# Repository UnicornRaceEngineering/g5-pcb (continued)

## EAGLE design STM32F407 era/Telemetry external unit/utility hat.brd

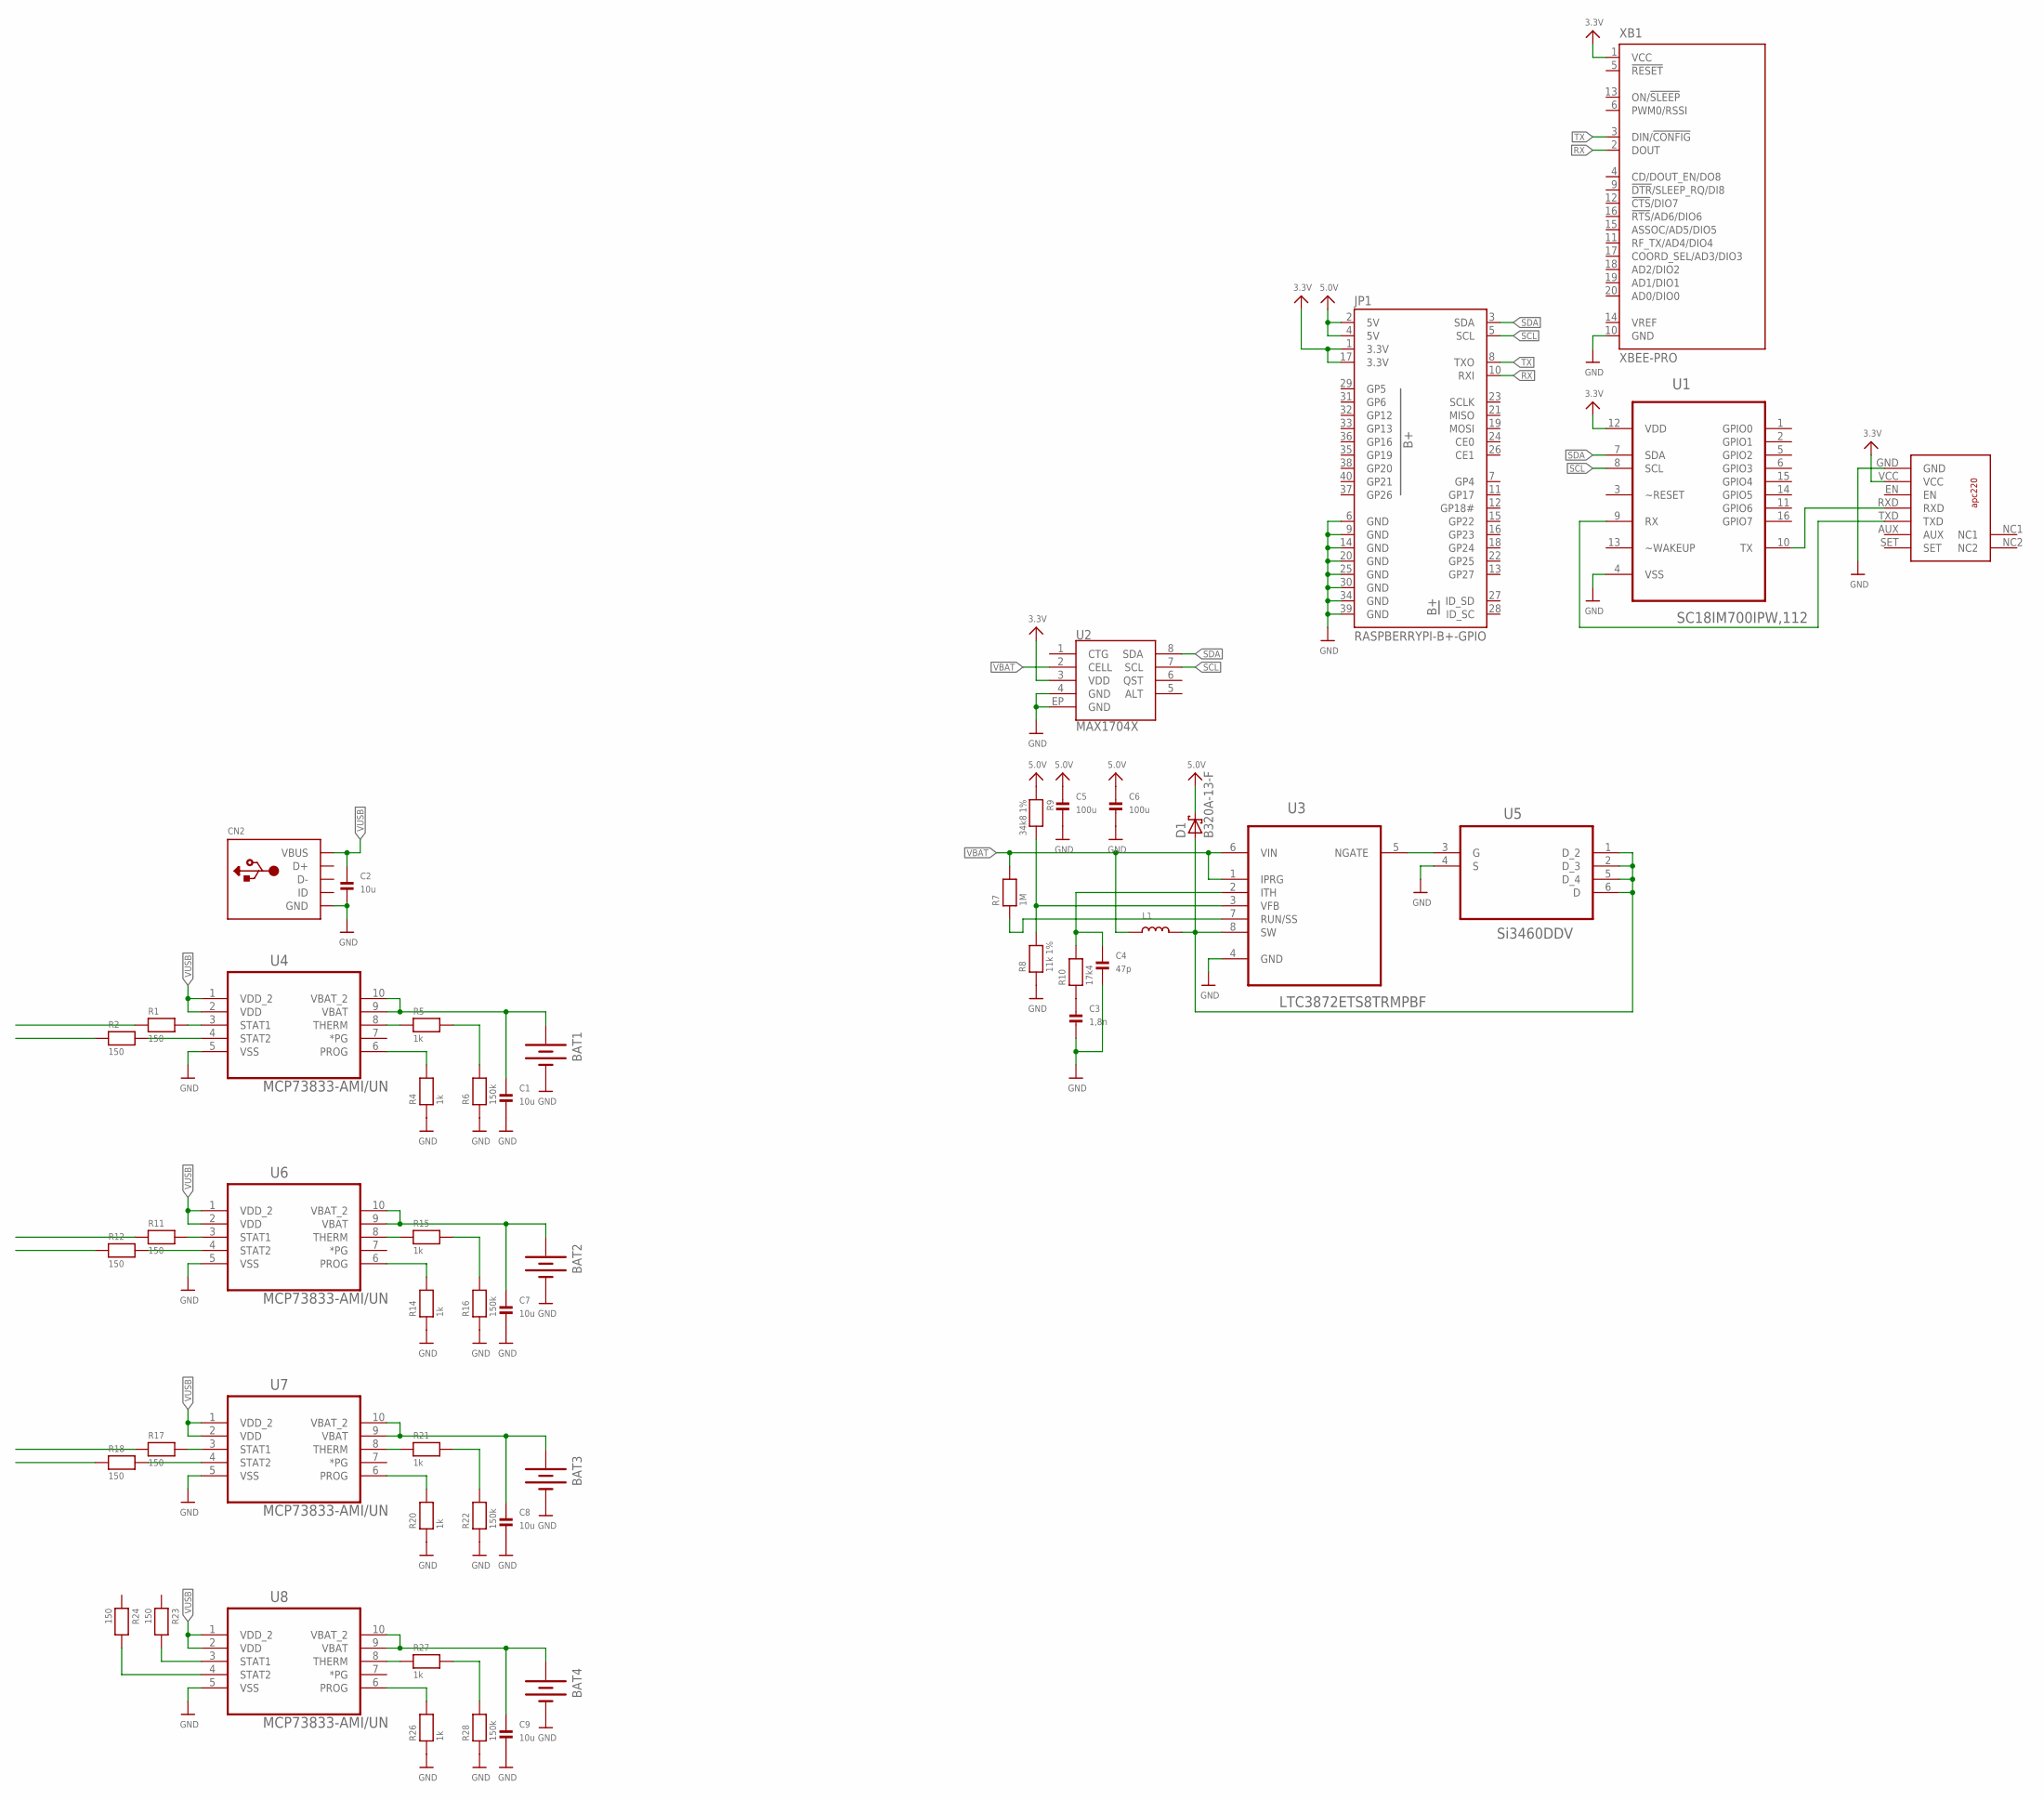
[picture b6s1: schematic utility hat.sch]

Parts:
BAT1, BAT2, BAT3, BAT4: BATTERY18650; BATTERY_18650-HOLDER
C1, C2, C7, C8, C9: 10u; _0805MP
C3: 1,8n; _0603MP
C4: 47p; _0603MP
C5, C6: 100u; 1206
CN2: USBMINIB; USB-MINIB
D1: B320A-13-F; SMC
JP1: RASPBERRYPI-B+-GPIO; 2X20-SHROUDED
L1: INDUCTOR; INDUCTOR_1007
R1, R2, R11, R12, R17, R18, R23, R24: 150; _0603MP
R4, R5, R14, R15, R20, R21, R26, R27: 1k; _0603MP
R6, R16, R22, R28: 150k; _0603MP
R7: 1M; _0603MP
R8: 11k 1%; _0603MP
R9: 34k8 1%; _0603MP
R10: 17k4; _0603MP
U1: SC18IM700IPW,112; SOP65P640X110-16N
U2: MAX1704X; TDFN-8
U3: LTC3872ETS8TRMPBF; SOT65P280X100-8N
U4, U6, U7, U8: MCP73833-AMI/UN; SOP50P490X110-10N
U5: Si3460DDV; SOT95P285X110-6N
U$10: APC220
XB1: XBEE-PRO

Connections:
3.3V: JP1.1 (3.3V), JP1.17 (3.3V), U1.12 (VDD), U2.3 (VDD), U$10.VCC, XB1.1 (VCC)
5.0V: C5.1, C6.1, D1.C, JP1.2 (5V), JP1.4 (5V), R9.1
GND: BAT1.GND@1 (-), BAT2.GND@1 (-), BAT3.GND@1 (-), BAT4.GND@1 (-), C1.2, C2.2, C3.2, C4.2, C5.2, C6.2, C7.2, C8.2, C9.2, CN2.GND, JP1.6 (GND), JP1.9 (GND), JP1.14 (GND), JP1.20 (GND), JP1.25 (GND), JP1.30 (GND), JP1.34 (GND), JP1.39 (GND), R4.1, R6.1, R8.1, R14.1, R16.1, R20.1, R22.1, R26.1, R28.1, U1.4 (VSS), U2.4 (GND), U2.EP (GND), U3.4 (GND), U4.5 (VSS), U5.4 (S), U6.5 (VSS), U7.5 (VSS), U8.5 (VSS), U$10.GND, XB1.10 (GND)
unnamed: U1.10 (TX), U$10.RXD
unnamed: U1.9 (RX), U$10.TXD
unnamed: R1.2, U4.3 (STAT1)
unnamed: R2.2, U4.4 (STAT2)
unnamed: R4.2, U4.6 (PROG)
unnamed: R5.1, U4.8 (THERM)
unnamed: R5.2, R6.2
unnamed: R7.1, U3.7 (RUN/SS)
unnamed: R8.2, R9.2, U3.3 (VFB)
unnamed: C4.1, R10.2, U3.2 (ITH)
unnamed: C3.1, R10.1
unnamed: D1.A, L1.P$2 (2), U3.8 (SW), U5.1 (D_2), U5.2 (D_3), U5.5 (D_4), U5.6 (D)
unnamed: U3.5 (NGATE), U5.3 (G)
unnamed: BAT1.PWR@1 (+), C1.1, U4.9 (VBAT), U4.10 (VBAT_2)
unnamed: R11.2, U6.3 (STAT1)
unnamed: R12.2, U6.4 (STAT2)
unnamed: R14.2, U6.6 (PROG)
unnamed: R15.1, U6.8 (THERM)
unnamed: R15.2, R16.2
unnamed: BAT2.PWR@1 (+), C7.1, U6.9 (VBAT), U6.10 (VBAT_2)
unnamed: R17.2, U7.3 (STAT1)
unnamed: R18.2, U7.4 (STAT2)
unnamed: R20.2, U7.6 (PROG)
unnamed: R21.1, U7.8 (THERM)
unnamed: R21.2, R22.2
unnamed: BAT3.PWR@1 (+), C8.1, U7.9 (VBAT), U7.10 (VBAT_2)
unnamed: R23.2, U8.3 (STAT1)
unnamed: R24.2, U8.4 (STAT2)
unnamed: R26.2, U8.6 (PROG)
unnamed: R27.1, U8.8 (THERM)
unnamed: R27.2, R28.2
unnamed: BAT4.PWR@1 (+), C9.1, U8.9 (VBAT), U8.10 (VBAT_2)
RX: JP1.10 (RXI), XB1.2 (DOUT)
SCL: JP1.5 (SCL), U1.8 (SCL), U2.7 (SCL)
SDA: JP1.3 (SDA), U1.7 (SDA), U2.8 (SDA)
TX: JP1.8 (TXO), XB1.3 (DIN/!CONFIG)
VBAT: L1.P$1 (1), R7.2, U2.2 (CELL), U3.1 (IPRG), U3.6 (VIN)
VUSB: C2.1, CN2.VBUS, U4.1 (VDD_2), U4.2 (VDD), U6.1 (VDD_2), U6.2 (VDD), U7.1 (VDD_2), U7.2 (VDD), U8.1 (VDD_2), U8.2 (VDD)

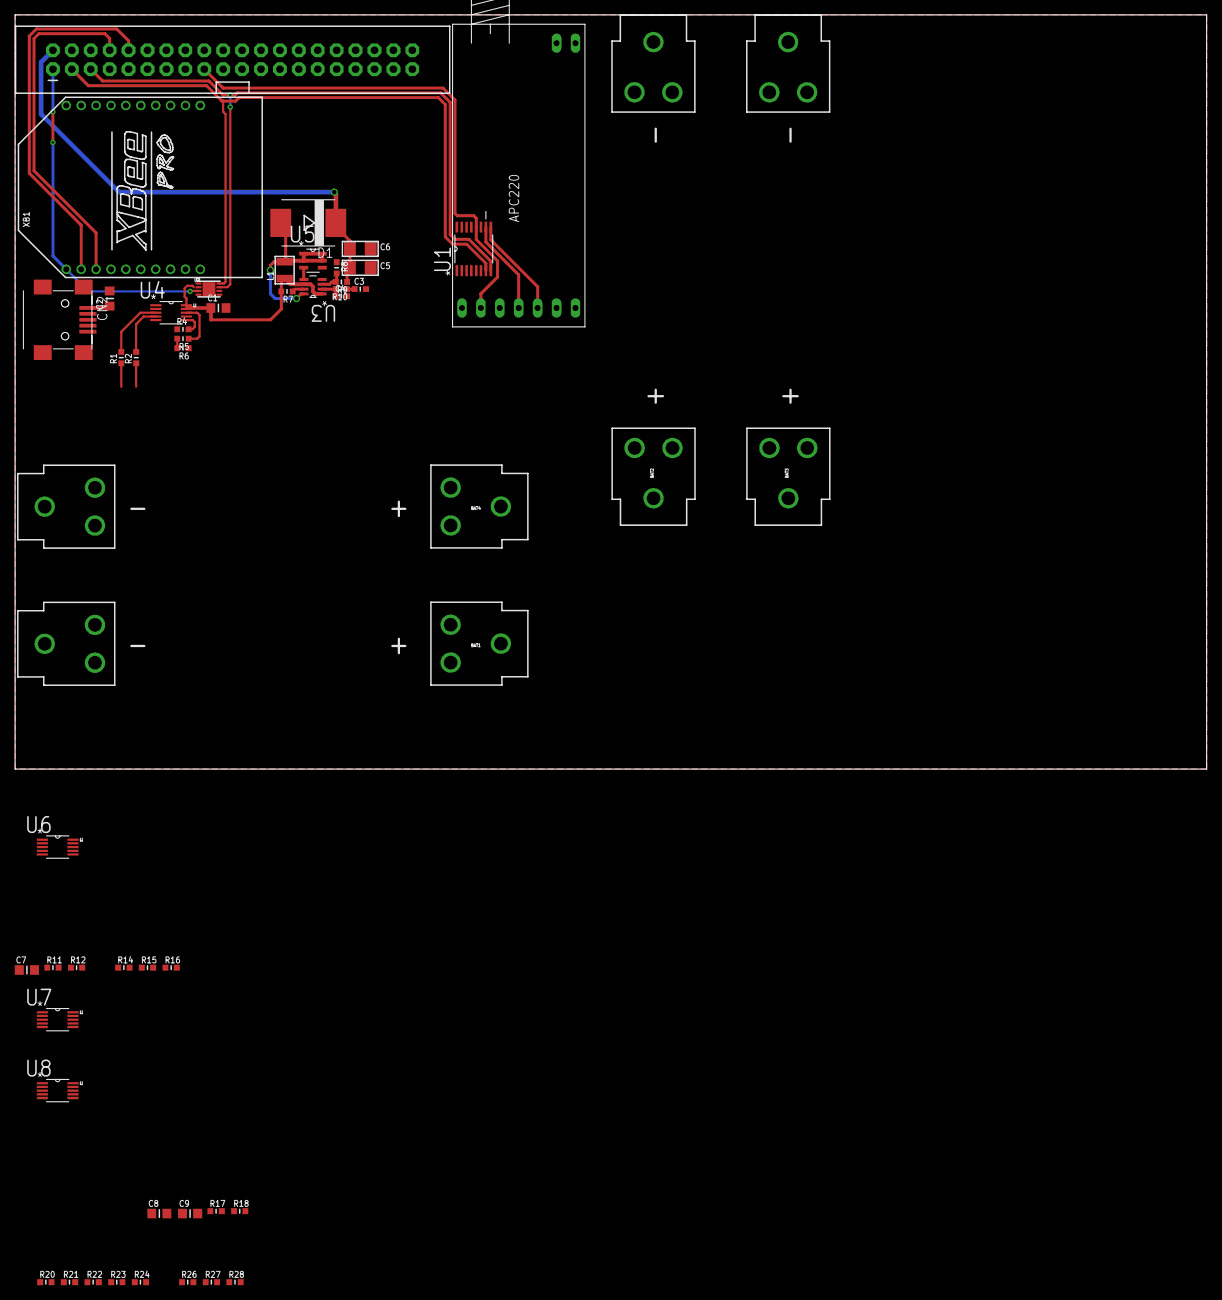
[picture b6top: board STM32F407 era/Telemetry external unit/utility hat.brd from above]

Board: 2 copper layers, 160.0 x 101.3 mm, 51 parts (0 on the bottom side), 41 nets.
